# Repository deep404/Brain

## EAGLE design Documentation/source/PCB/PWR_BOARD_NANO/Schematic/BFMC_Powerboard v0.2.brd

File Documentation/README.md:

# BFMC - Documentation Project

This repo contains the sources for the Bosch Future Mobility Challenge documentation. 
Find it at this [link](https://bosch-future-mobility-challenge-documentation.readthedocs-hosted.com)

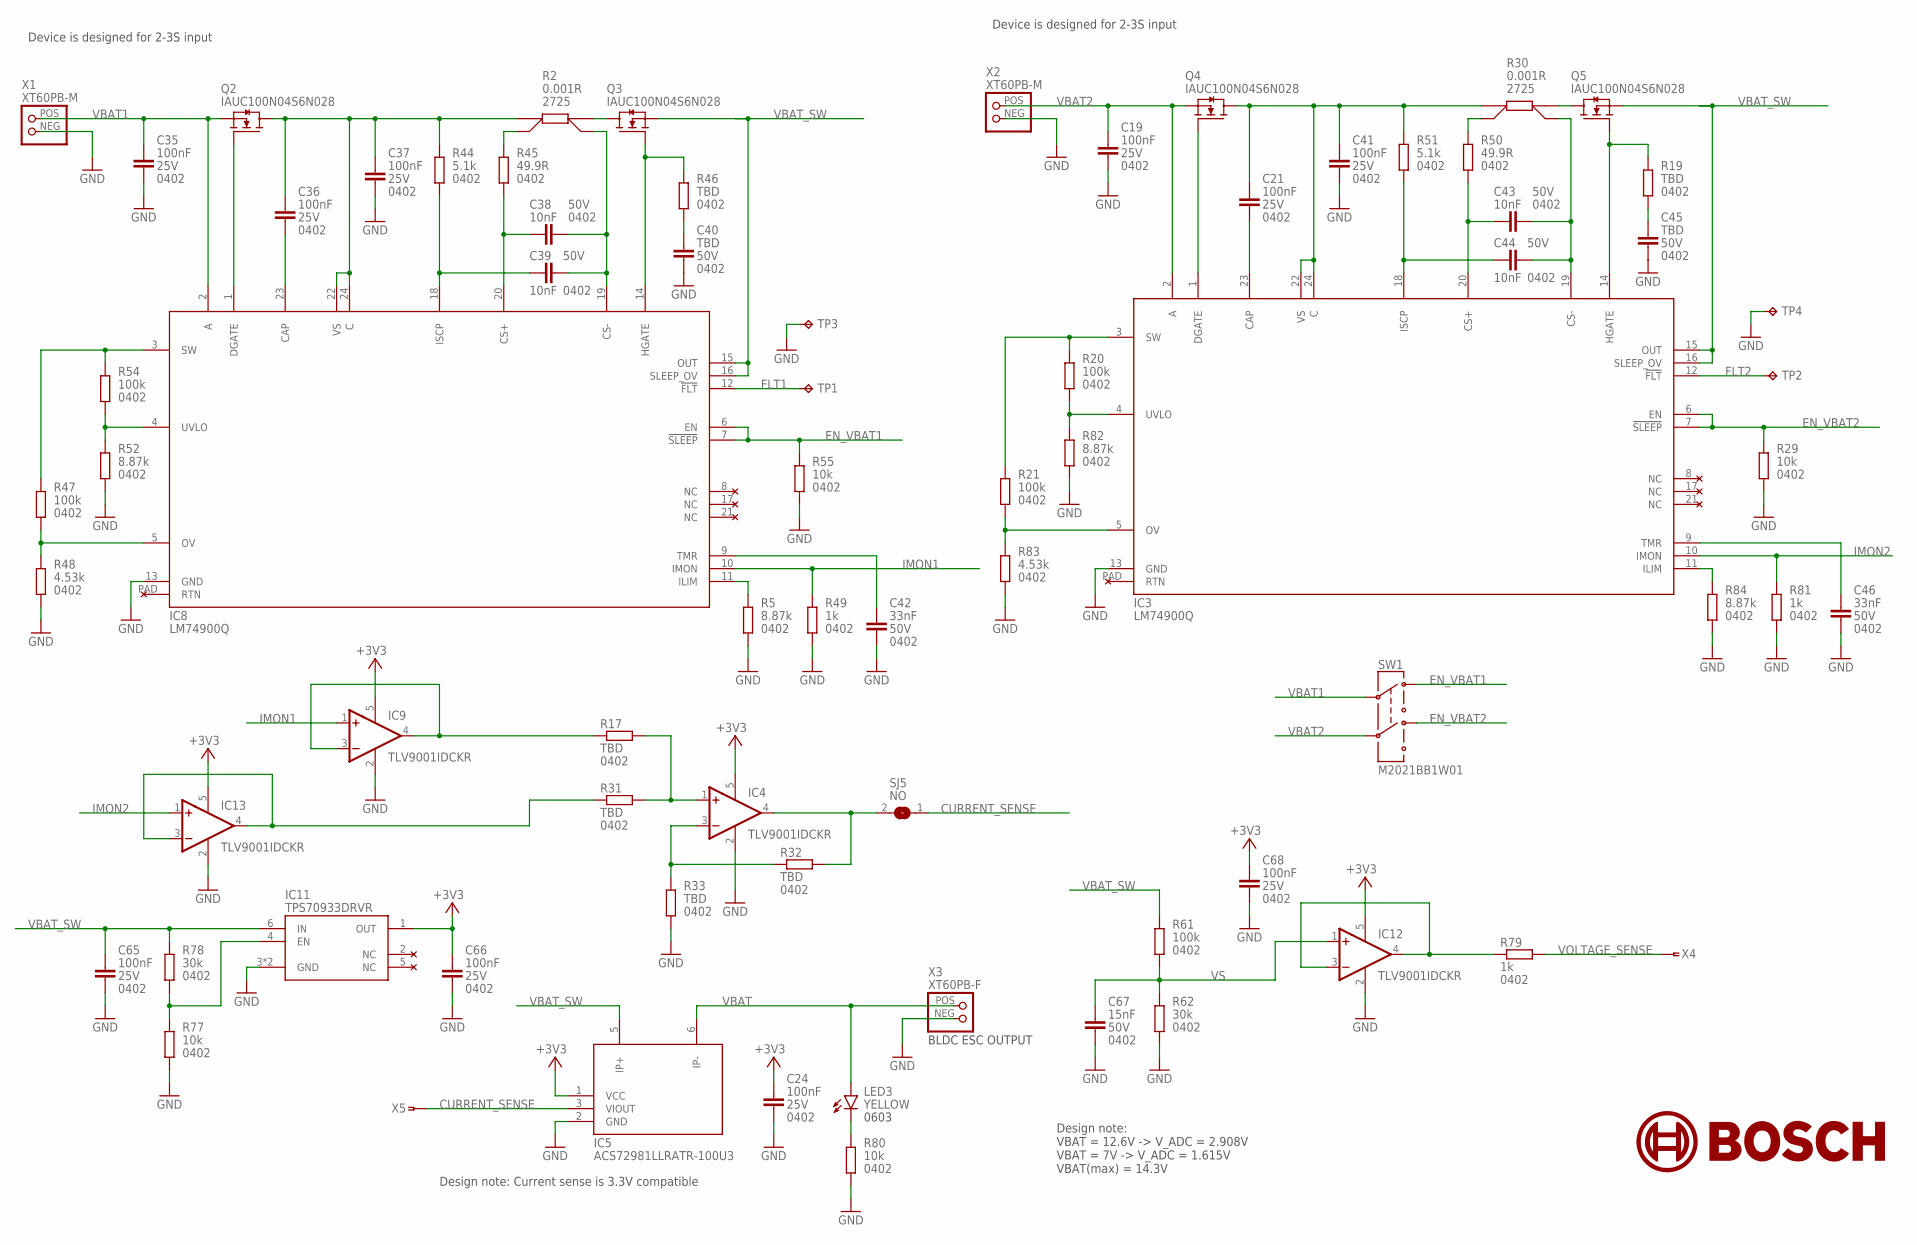
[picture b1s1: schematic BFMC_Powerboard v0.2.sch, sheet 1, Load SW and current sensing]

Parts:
C19, C21, C24, C35, C36, C37, C41, C65, C66, C68: 100nF; C0402_IPC
C38, C39, C43, C44: 10nF; C0402_IPC
C40, C45: TBD; C0402_IPC
C42, C46: 33nF; C0402_IPC
C67: 15nF; C0402_IPC
IC3, IC8: LM74900Q; QFN24-4X4
IC4, IC9, IC12, IC13: TLV9001IDCKR; SC70-5
IC5: ACS72981LLRATR-100U3; ACS72981
IC11: TPS70933DRVR; WSON6_2X2MM_NO_SILK
LED3: YELLOW; CHIPLED_0603
Q2, Q3, Q4, Q5: IAUC100N04S6N028; PG-TDSON-8
R2, R30: 0.001R; CRS272
R5, R52, R82, R84: 8.87k; R0402_IPC
R17, R19, R31, R32, R33, R46: TBD; R0402_IPC
R20, R21, R47, R54, R61: 100k; R0402_IPC
R29, R55, R77, R80: 10k; R0402_IPC
R44, R51: 5.1k; R0402_IPC
R45, R50: 49.9R; R0402_IPC
R48, R83: 4.53k; R0402_IPC
R49, R79, R81: 1k; R0402_IPC
R62, R78: 30k; R0402_IPC
SJ5: NO; SJ_1X1.5_NO
SW1: M2021BB1W01
TP1, TP2, TP3, TP4: TPTP13R; TP13R
X1, X2: XT60PB-M; XT60PB
X3: XT60PB-F; XT60PB
X4, X5: ZFKDSA1-W-6,35; 1704994

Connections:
+3V3: C24.1, C66.1, C68.1, IC4.5 (V+), IC5.1 (VCC), IC9.5 (V+), IC11.1 (OUT), IC12.5 (V+), IC13.5 (V+); also elsewhere on the board
CURRENT_SENSE: IC5.3 (VIOUT), SJ5.1, X5.1, X5.2
EN_VBAT1: IC8.6 (EN), IC8.7 (!SLEEP), R55.2, SW1.3
EN_VBAT2: IC3.6 (EN), IC3.7 (!SLEEP), R29.2, SW1.6
FLT1: IC8.12 (!FLT), TP1.TP
FLT2: IC3.12 (!FLT), TP2.TP
GND: C19.2, C24.2, C35.2, C37.2, C40.1, C41.2, C42.2, C45.1, C46.2, C65.2, C66.2, C67.2, C68.2, IC3.13 (GND), IC4.2 (V-), IC5.2 (GND), IC8.13 (GND), IC9.2 (V-), IC11.3 (GND), IC11.EP (GND), IC12.2 (V-), IC13.2 (V-), R5.1, R29.1, R33.1, R48.1, R49.1, R52.1, R55.1, R62.1, R77.1, R80.1, R81.1, R82.1, R83.1, R84.1, TP3.TP, TP4.TP, X1.NEG (2), X2.NEG (2), X3.NEG (2); also elsewhere on the board
IMON1: IC8.10 (IMON), IC9.1 (+IN), R49.2
IMON2: IC3.10 (IMON), IC13.1 (+IN), R81.2
unnamed: IC8.1 (DGATE), Q2.4 (G)
unnamed: IC3.1 (DGATE), Q4.4 (G)
unnamed: C21.2, IC3.23 (CAP)
unnamed: C21.1, C41.1, IC3.22 (VS), IC3.24 (C), Q4.5 (D), Q4.6 (D), Q4.7 (D), Q4.8 (D), Q4.TH (D), R30.1A, R51.2
unnamed: IC3.14 (HGATE), Q5.4 (G), R19.2
unnamed: IC4.1 (+IN), R17.2, R31.2
unnamed: C44.1, IC3.18 (ISCP), R51.1
unnamed: R30.1B, R50.2
unnamed: C43.2, C44.2, IC3.19 (CS-), R30.2B
unnamed: Q5.5 (D), Q5.6 (D), Q5.7 (D), Q5.8 (D), Q5.TH (D), R30.2A
unnamed: IC4.4 (OUT), R32.2, SJ5.2
unnamed: C43.1, IC3.20 (CS+), R50.1
unnamed: C45.2, R19.1
unnamed: IC4.3 (-IN), R32.1, R33.2
unnamed: IC9.3 (-IN), IC9.4 (OUT), R17.1
unnamed: IC13.3 (-IN), IC13.4 (OUT), R31.1
unnamed: C36.2, IC8.23 (CAP)
unnamed: C36.1, C37.1, IC8.22 (VS), IC8.24 (C), Q2.5 (D), Q2.6 (D), Q2.7 (D), Q2.8 (D), Q2.TH (D), R2.1A, R44.2
unnamed: IC8.14 (HGATE), Q3.4 (G), R46.2
unnamed: C39.1, IC8.18 (ISCP), R44.1
unnamed: IC8.3 (SW), R47.2, R54.2
unnamed: R2.1B, R45.2
unnamed: C38.2, C39.2, IC8.19 (CS-), R2.2B
unnamed: Q3.5 (D), Q3.6 (D), Q3.7 (D), Q3.8 (D), Q3.TH (D), R2.2A
unnamed: C38.1, IC8.20 (CS+), R45.1
unnamed: C40.2, R46.1
unnamed: IC8.11 (ILIM), R5.2
unnamed: IC3.11 (ILIM), R84.2
unnamed: C42.1, IC8.9 (TMR)
unnamed: IC8.4 (UVLO), R52.2, R54.1
unnamed: IC8.5 (OV), R47.1, R48.2
unnamed: IC12.3 (-IN), IC12.4 (OUT), R79.1
unnamed: LED3.C, R80.2
unnamed: IC11.4 (EN), R77.2, R78.1
unnamed: C46.1, IC3.9 (TMR)
unnamed: IC3.3 (SW), R20.2, R21.2
unnamed: IC3.4 (UVLO), R20.1, R82.2
unnamed: IC3.5 (OV), R21.1, R83.2
VBAT: IC5.6 (IP-), LED3.A, X3.POS (1); also elsewhere on the board
VBAT1: C35.1, IC8.2 (A), Q2.1 (S), Q2.2 (S), Q2.3 (S), SW1.2, X1.POS (1)
VBAT2: C19.1, IC3.2 (A), Q4.1 (S), Q4.2 (S), Q4.3 (S), SW1.5, X2.POS (1)
VBAT_SW: C65.1, IC3.15 (OUT), IC3.16 (SLEEP_OV), IC5.5 (IP+), IC8.15 (OUT), IC8.16 (SLEEP_OV), IC11.6 (IN), Q3.1 (S), Q3.2 (S), Q3.3 (S), Q5.1 (S), Q5.2 (S), Q5.3 (S), R61.2, R78.2
VOLTAGE_SENSE: R79.2, X4.1, X4.2
VS: C67.1, IC12.1 (+IN), R61.1, R62.2

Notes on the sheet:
BLDC ESC OUTPUT
Device is designed for 2-3S input
Design note: Current sense is 3.3V compatible
Design note: VBAT = 12.6V -> V_ADC = 2.908V VBAT = 7V -> V_ADC = 1.615V VBAT(max) = 14.3V

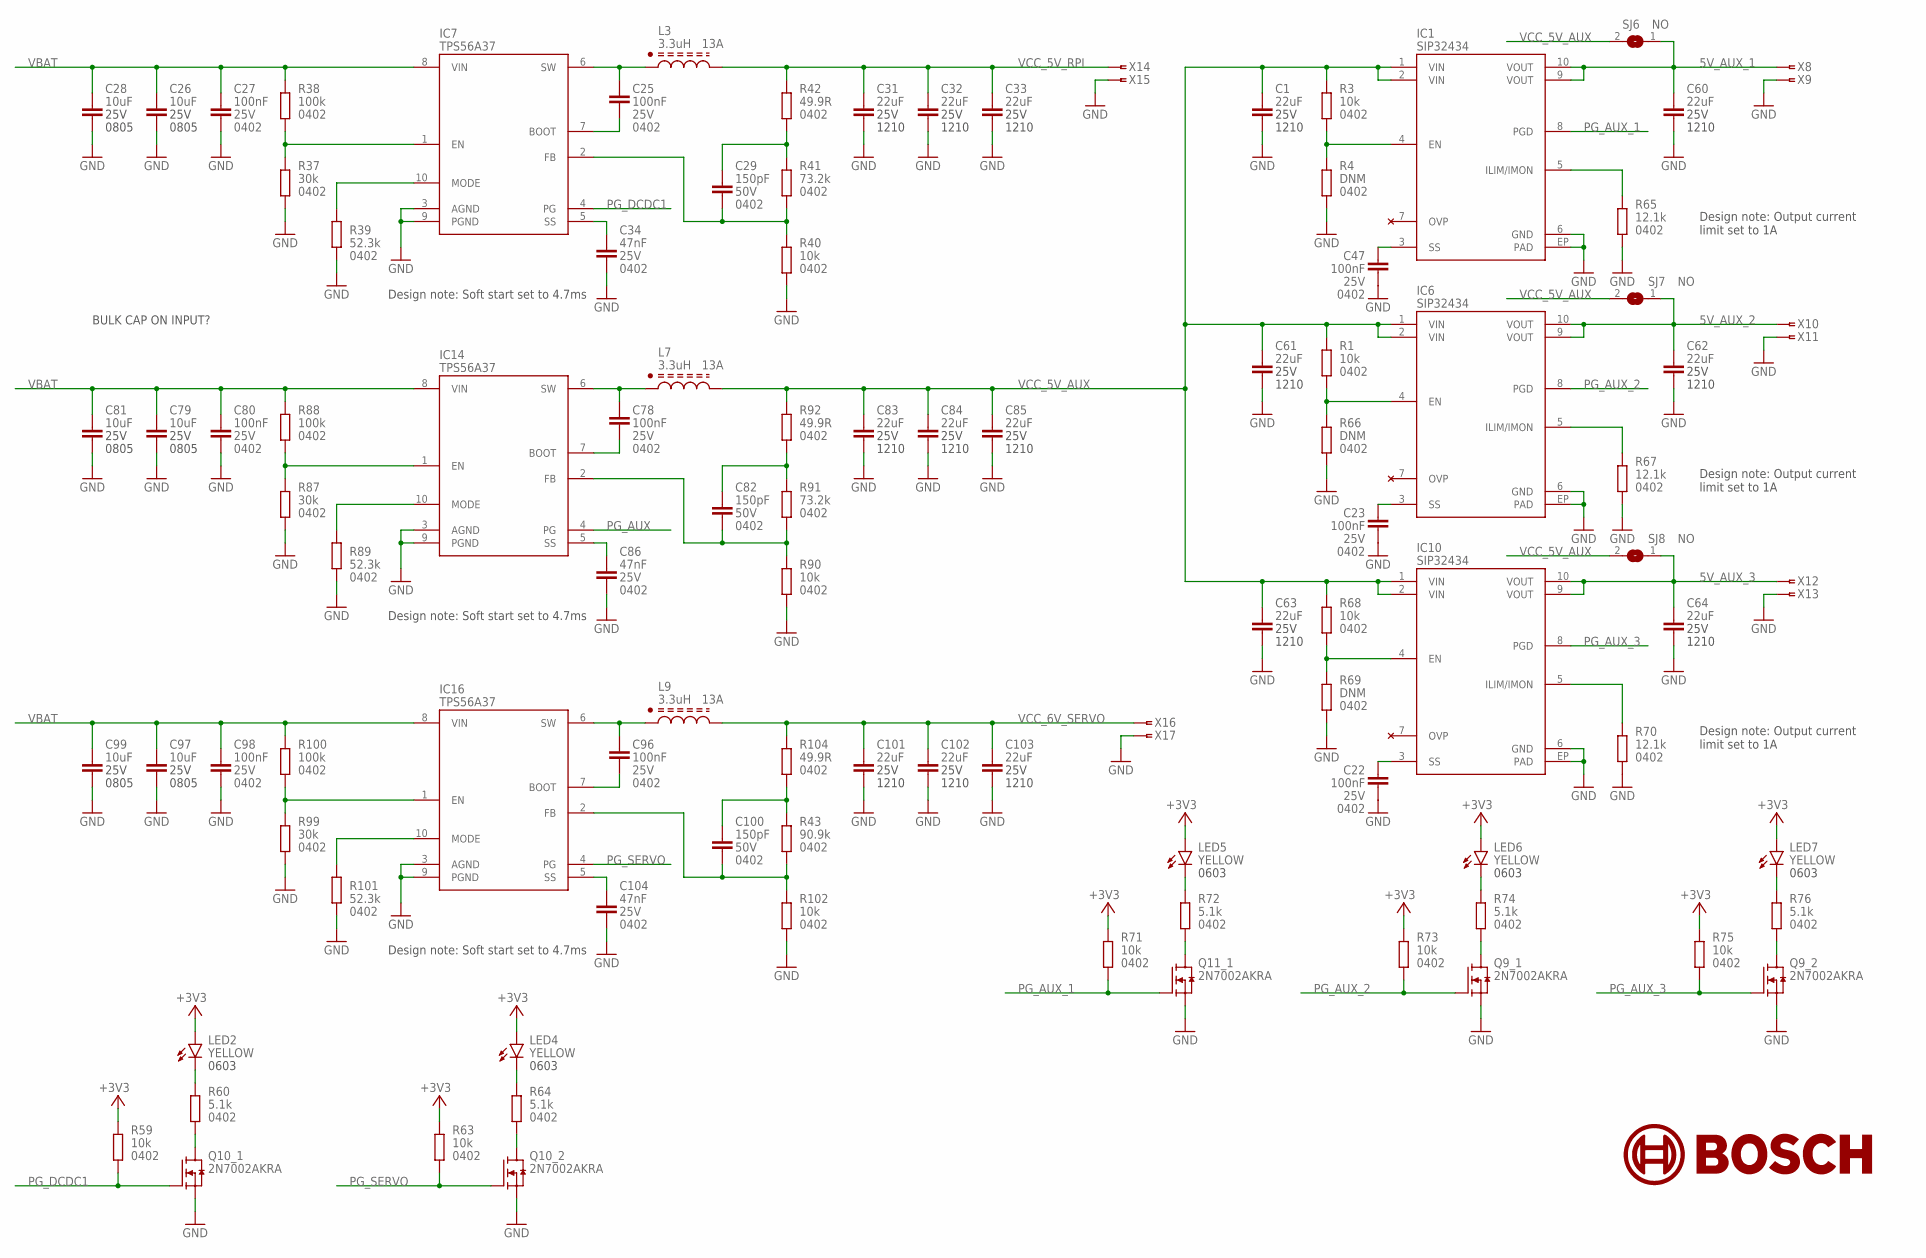
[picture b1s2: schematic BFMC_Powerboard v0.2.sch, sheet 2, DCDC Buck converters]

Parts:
C1, C31, C32, C33, C60, C61, C62, C63, C64, C83, C84, C85, C101, C102, C103: 22uF; C1210
C22, C23, C25, C27, C47, C78, C80, C96, C98: 100nF; C0402_IPC
C26, C28, C79, C81, C97, C99: 10uF; C0805
C29, C82, C100: 150pF; C0402_IPC
C34, C86, C104: 47nF; C0402_IPC
IC1, IC6, IC10: SIP32434; DFN10-3X3
IC7, IC14, IC16: TPS56A37; VQFN-HR-RPA
L3, L7, L9: 3.3uH; EXLA1V0705
LED2, LED4, LED5, LED6, LED7: YELLOW; CHIPLED_0603
Q9, Q10, Q11: 2N7002AKRA; DFN1412-6
R1, R3, R40, R59, R63, R68, R71, R73, R75, R90, R102: 10k; R0402_IPC
R4, R66, R69: DNM; R0402_IPC
R37, R87, R99: 30k; R0402_IPC
R38, R88, R100: 100k; R0402_IPC
R39, R89, R101: 52.3k; R0402_IPC
R41, R91: 73.2k; R0402_IPC
R42, R92, R104: 49.9R; R0402_IPC
R43: 90.9k; R0402_IPC
R60, R64, R72, R74, R76: 5.1k; R0402_IPC
R65, R67, R70: 12.1k; R0402_IPC
SJ6, SJ7, SJ8: NO; SJ_1X1.5_NO
X8, X9, X10, X11, X12, X13, X14, X15, X16, X17: ZFKDSA1-W-6,35; 1704994

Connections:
5V_AUX_1: C60.1, IC1.9 (VOUT), IC1.10 (VOUT), SJ6.1, X8.1, X8.2
5V_AUX_2: C62.1, IC6.9 (VOUT), IC6.10 (VOUT), SJ7.1, X10.1, X10.2
5V_AUX_3: C64.1, IC10.9 (VOUT), IC10.10 (VOUT), SJ8.1, X12.1, X12.2
+3V3: LED2.A, LED4.A, LED5.A, LED6.A, LED7.A, R59.2, R63.2, R71.2, R73.2, R75.2; also elsewhere on the board
GND: C1.2, C22.2, C23.2, C26.2, C27.2, C28.2, C31.2, C32.2, C33.2, C34.2, C47.2, C60.2, C61.2, C62.2, C63.2, C64.2, C79.2, C80.2, C81.2, C83.2, C84.2, C85.2, C86.2, C97.2, C98.2, C99.2, C101.2, C102.2, C103.2, C104.2, IC1.6 (GND), IC1.EP (PAD), IC6.6 (GND), IC6.EP (PAD), IC7.3 (AGND), IC7.9 (PGND), IC10.6 (GND), IC10.EP (PAD), IC14.3 (AGND), IC14.9 (PGND), IC16.3 (AGND), IC16.9 (PGND), Q9.1 (S), Q9.4 (S), Q10.1 (S), Q10.4 (S), Q11.1 (S), R4.1, R37.1, R39.1, R40.1, R65.1, R66.1, R67.1, R69.1, R70.1, R87.1, R89.1, R90.1, R99.1, R101.1, R102.1, X9.1, X9.2, X11.1, X11.2, X13.1, X13.2, X15.1, X15.2, X17.1, X17.2; also elsewhere on the board
unnamed: IC6.5 (ILIM/IMON), R67.2
unnamed: IC1.5 (ILIM/IMON), R65.2
unnamed: IC1.4 (EN), R3.1, R4.2
unnamed: C22.1, IC10.3 (SS)
unnamed: C23.1, IC6.3 (SS)
unnamed: C47.1, IC1.3 (SS)
unnamed: C25.1, IC7.6 (SW), L3.1
unnamed: C25.2, IC7.7 (BOOT)
unnamed: C34.1, IC7.5 (SS)
unnamed: IC7.1 (EN), R37.2, R38.1
unnamed: C29.2, IC7.2 (FB), R40.2, R41.1
unnamed: IC7.10 (MODE), R39.2
unnamed: C29.1, R41.2, R42.1
unnamed: Q10.6 (D), Q10.7 (D), R60.1
unnamed: LED2.C, R60.2
unnamed: Q10.3 (D), Q10.8 (D), R64.1
unnamed: LED4.C, R64.2
unnamed: IC6.4 (EN), R1.1, R66.2
unnamed: IC10.5 (ILIM/IMON), R70.2
unnamed: IC10.4 (EN), R68.1, R69.2
unnamed: Q11.6 (D), Q11.7 (D), R72.1
unnamed: LED5.C, R72.2
unnamed: Q9.6 (D), Q9.7 (D), R74.1
unnamed: LED6.C, R74.2
unnamed: Q9.3 (D), Q9.8 (D), R76.1
unnamed: LED7.C, R76.2
unnamed: C78.1, IC14.6 (SW), L7.1
unnamed: C78.2, IC14.7 (BOOT)
unnamed: IC14.1 (EN), R87.2, R88.1
unnamed: IC14.10 (MODE), R89.2
unnamed: C82.2, IC14.2 (FB), R90.2, R91.1
unnamed: C82.1, R91.2, R92.1
unnamed: C86.1, IC14.5 (SS)
unnamed: C96.1, IC16.6 (SW), L9.1
unnamed: C96.2, IC16.7 (BOOT)
unnamed: IC16.1 (EN), R99.2, R100.1
unnamed: IC16.10 (MODE), R101.2
unnamed: C100.2, IC16.2 (FB), R43.1, R102.2
unnamed: C100.1, R43.2, R104.1
unnamed: C104.1, IC16.5 (SS)
PG_AUX: IC14.4 (PG)
PG_AUX_1: IC1.8 (PGD), Q11.2 (G), R71.1
PG_AUX_2: IC6.8 (PGD), Q9.2 (G), R73.1
PG_AUX_3: IC10.8 (PGD), Q9.5 (G), R75.1
PG_DCDC1: IC7.4 (PG), Q10.2 (G), R59.1
PG_SERVO: IC16.4 (PG), Q10.5 (G), R63.1
VBAT: C26.1, C27.1, C28.1, C79.1, C80.1, C81.1, C97.1, C98.1, C99.1, IC7.8 (VIN), IC14.8 (VIN), IC16.8 (VIN), R38.2, R88.2, R100.2; also elsewhere on the board
VCC_5V_AUX: C1.1, C61.1, C63.1, C83.1, C84.1, C85.1, IC1.1 (VIN), IC1.2 (VIN), IC6.1 (VIN), IC6.2 (VIN), IC10.1 (VIN), IC10.2 (VIN), L7.2, R1.2, R3.2, R68.2, R92.2, SJ6.2, SJ7.2, SJ8.2; also elsewhere on the board
VCC_5V_RPI: C31.1, C32.1, C33.1, L3.2, R42.2, X14.1, X14.2
VCC_6V_SERVO: C101.1, C102.1, C103.1, L9.2, R104.2, X16.1, X16.2

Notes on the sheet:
Design note: Soft start set to 4.7ms
BULK CAP ON INPUT?
Design note: Output current limit set to 1A

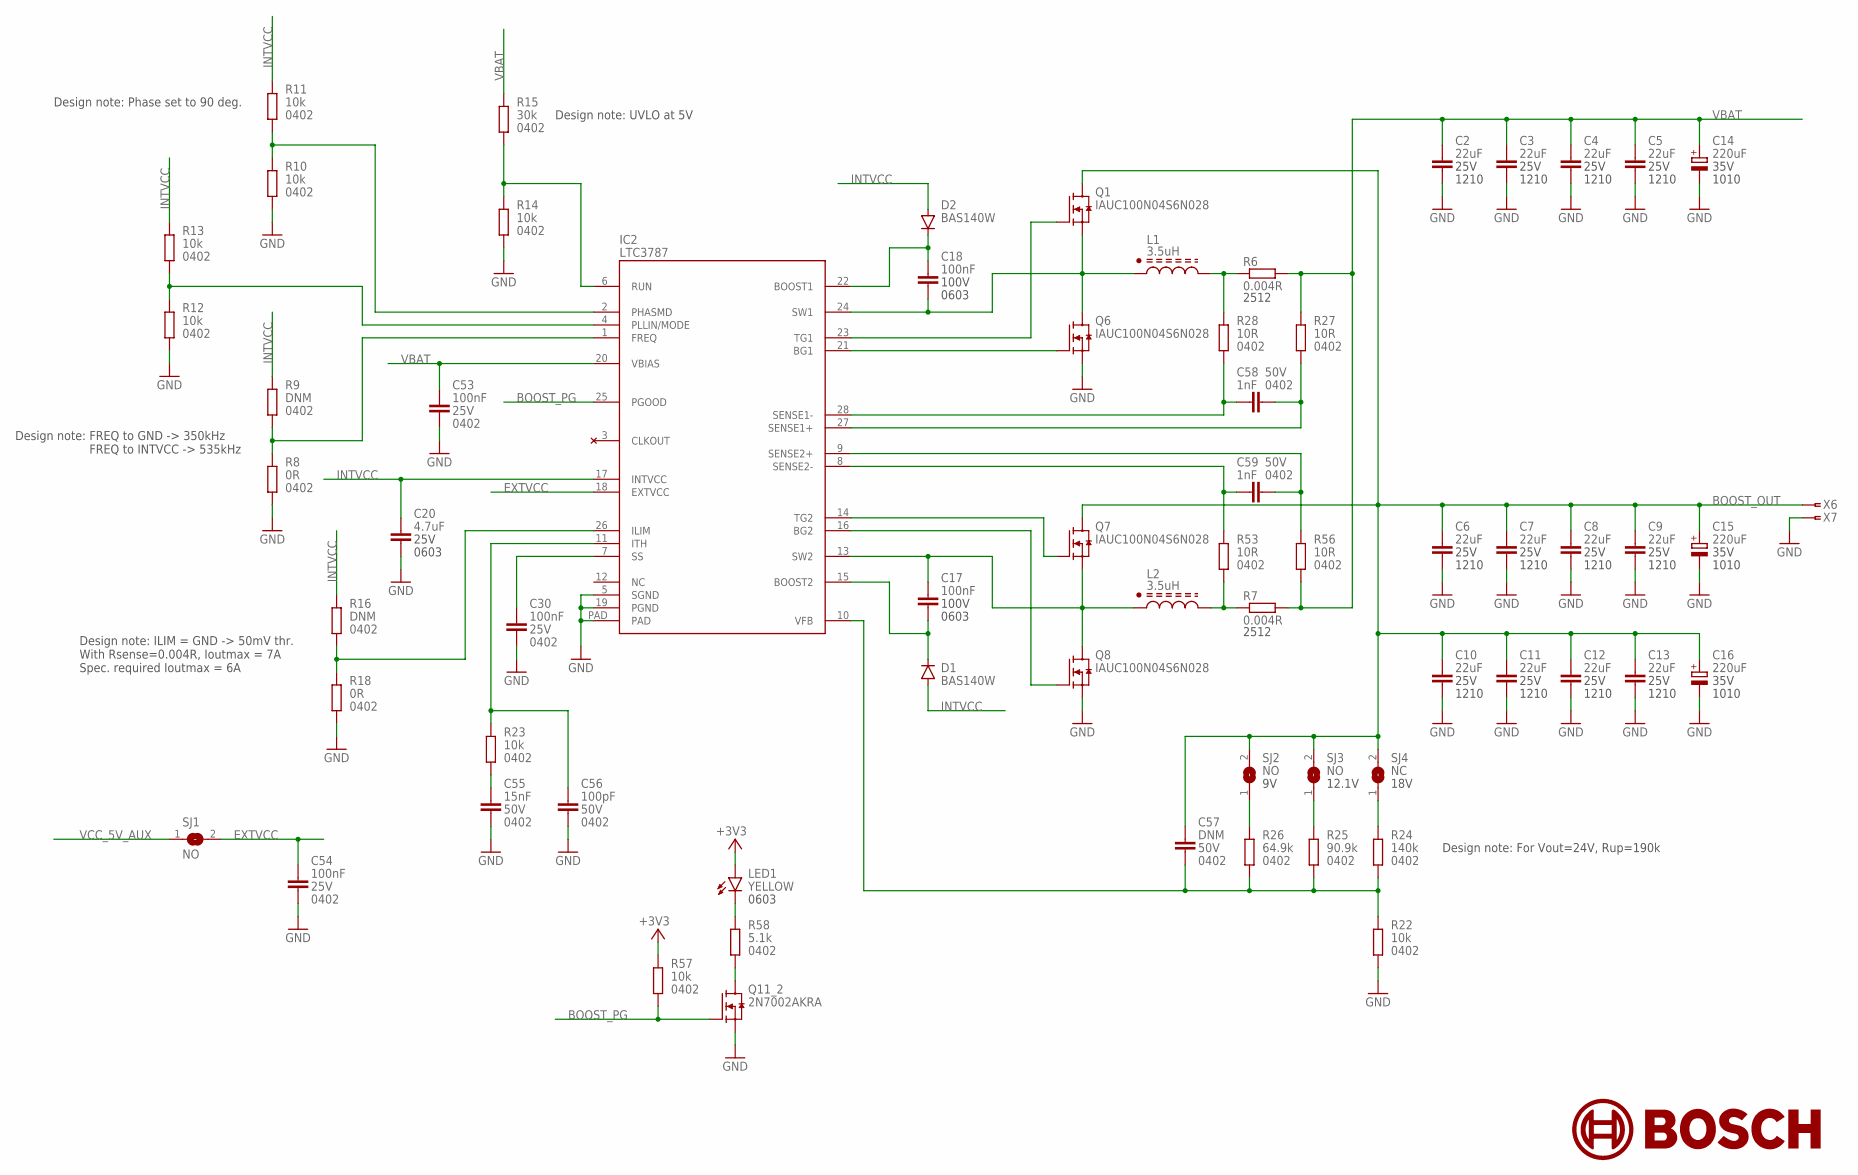
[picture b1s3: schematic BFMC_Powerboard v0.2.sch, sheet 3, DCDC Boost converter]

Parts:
C2, C3, C4, C5, C6, C7, C8, C9, C10, C11, C12, C13: 22uF; C1210
C14, C15, C16: 220uF; CAP_POL_1010
C17, C18: 100nF; C0603
C20: 4.7uF; C0603
C30, C53, C54: 100nF; C0402_IPC
C55: 15nF; C0402_IPC
C56: 100pF; C0402_IPC
C57: DNM; C0402_IPC
C58, C59: 1nF; C0402_IPC
D1, D2: BAS140W; SOD323-R
IC2: LTC3787; UFD-QFN28-4X5MM
L1, L2: 3.5uH; 7447709003
LED1: YELLOW; CHIPLED_0603
Q1, Q6, Q7, Q8: IAUC100N04S6N028; PG-TDSON-8
Q11: 2N7002AKRA; DFN1412-6
R6, R7: 0.004R; R2512
R8, R18: 0R; R0402_IPC
R9, R16: DNM; R0402_IPC
R10, R11, R12, R13, R14, R22, R23, R57: 10k; R0402_IPC
R15: 30k; R0402_IPC
R24: 140k; R0402_IPC
R25: 90.9k; R0402_IPC
R26: 64.9k; R0402_IPC
R27, R28, R53, R56: 10R; R0402_IPC
R58: 5.1k; R0402_IPC
SJ1, SJ2, SJ3: NO; SJ_1X1.5_NO
SJ4: NC; SJ_1X1.5_NO
X6, X7: ZFKDSA1-W-6,35; 1704994

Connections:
+3V3: LED1.A, R57.2; also elsewhere on the board
BOOST_OUT: C6.1, C7.1, C8.1, C9.1, C10.1, C11.1, C12.1, C13.1, C15.2 (+), C16.2 (+), C57.1, Q1.5 (D), Q1.6 (D), Q1.7 (D), Q1.8 (D), Q1.TH (D), Q7.5 (D), Q7.6 (D), Q7.7 (D), Q7.8 (D), Q7.TH (D), SJ2.2, SJ3.2, SJ4.2, X6.1, X6.2
BOOST_PG: IC2.25 (PGOOD), Q11.5 (G), R57.1
EXTVCC: C54.1, IC2.18 (EXTVCC), SJ1.2
GND: C2.2, C3.2, C4.2, C5.2, C6.2, C7.2, C8.2, C9.2, C10.2, C11.2, C12.2, C13.2, C14.1 (-), C15.1 (-), C16.1 (-), C20.2, C30.2, C53.2, C54.2, C55.2, C56.2, IC2.5 (SGND), IC2.19 (PGND), IC2.PAD, Q6.1 (S), Q6.2 (S), Q6.3 (S), Q8.1 (S), Q8.2 (S), Q8.3 (S), Q11.4 (S), R8.1, R10.1, R12.1, R14.1, R18.1, R22.1, X7.1, X7.2; also elsewhere on the board
INTVCC: C20.1, D1.A, D2.A, IC2.17 (INTVCC), R9.2, R11.2, R13.2, R16.2
unnamed: IC2.23 (TG1), Q1.4 (G)
unnamed: IC2.21 (BG1), Q6.4 (G)
unnamed: IC2.14 (TG2), Q7.4 (G)
unnamed: IC2.16 (BG2), Q8.4 (G)
unnamed: C17.1, IC2.13 (SW2), L2.1, Q7.1 (S), Q7.2 (S), Q7.3 (S), Q8.5 (D), Q8.6 (D), Q8.7 (D), Q8.8 (D), Q8.TH (D)
unnamed: C18.2, IC2.24 (SW1), L1.1, Q1.1 (S), Q1.2 (S), Q1.3 (S), Q6.5 (D), Q6.6 (D), Q6.7 (D), Q6.8 (D), Q6.TH (D)
unnamed: C58.1, IC2.28 (SENSE1-), R28.1
unnamed: C59.1, IC2.8 (SENSE2-), R53.2
unnamed: C17.2, D1.C, IC2.15 (BOOST2)
unnamed: C18.1, D2.C, IC2.22 (BOOST1)
unnamed: IC2.1 (FREQ), R8.2, R9.1
unnamed: IC2.4 (PLLIN/MODE), R12.2, R13.1
unnamed: C57.2, IC2.10 (VFB), R22.2, R24.2, R25.1, R26.1
unnamed: IC2.2 (PHASMD), R10.2, R11.1
unnamed: C30.1, IC2.7 (SS)
unnamed: IC2.6 (RUN), R14.2, R15.1
unnamed: C56.1, IC2.11 (ITH), R23.2
unnamed: IC2.26 (ILIM), R16.1, R18.2
unnamed: C55.1, R23.1
unnamed: R24.1, SJ4.1
unnamed: R26.2, SJ2.1
unnamed: R25.2, SJ3.1
unnamed: L1.2, R6.1, R28.2
unnamed: C58.2, IC2.27 (SENSE1+), R27.1
unnamed: L2.2, R7.1, R53.1
unnamed: C59.2, IC2.9 (SENSE2+), R56.2
unnamed: Q11.3 (D), Q11.8 (D), R58.1
unnamed: LED1.C, R58.2
VBAT: C2.1, C3.1, C4.1, C5.1, C14.2 (+), C53.1, IC2.20 (VBIAS), R6.2, R7.2, R15.2, R27.2, R56.1; also elsewhere on the board
VCC_5V_AUX: SJ1.1; also elsewhere on the board

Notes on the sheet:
Design note: FREQ to GND -> 350kHz FREQ to INTVCC -> 535kHz
Design note: Phase set to 90 deg.
Design note: UVLO at 5V
Design note: ILIM = GND -> 50mV thr. With Rsense=0.004R, Ioutmax = 7A Spec. required Ioutmax = 6A
12.1V
18V
Design note: For Vout=24V, Rup=190k

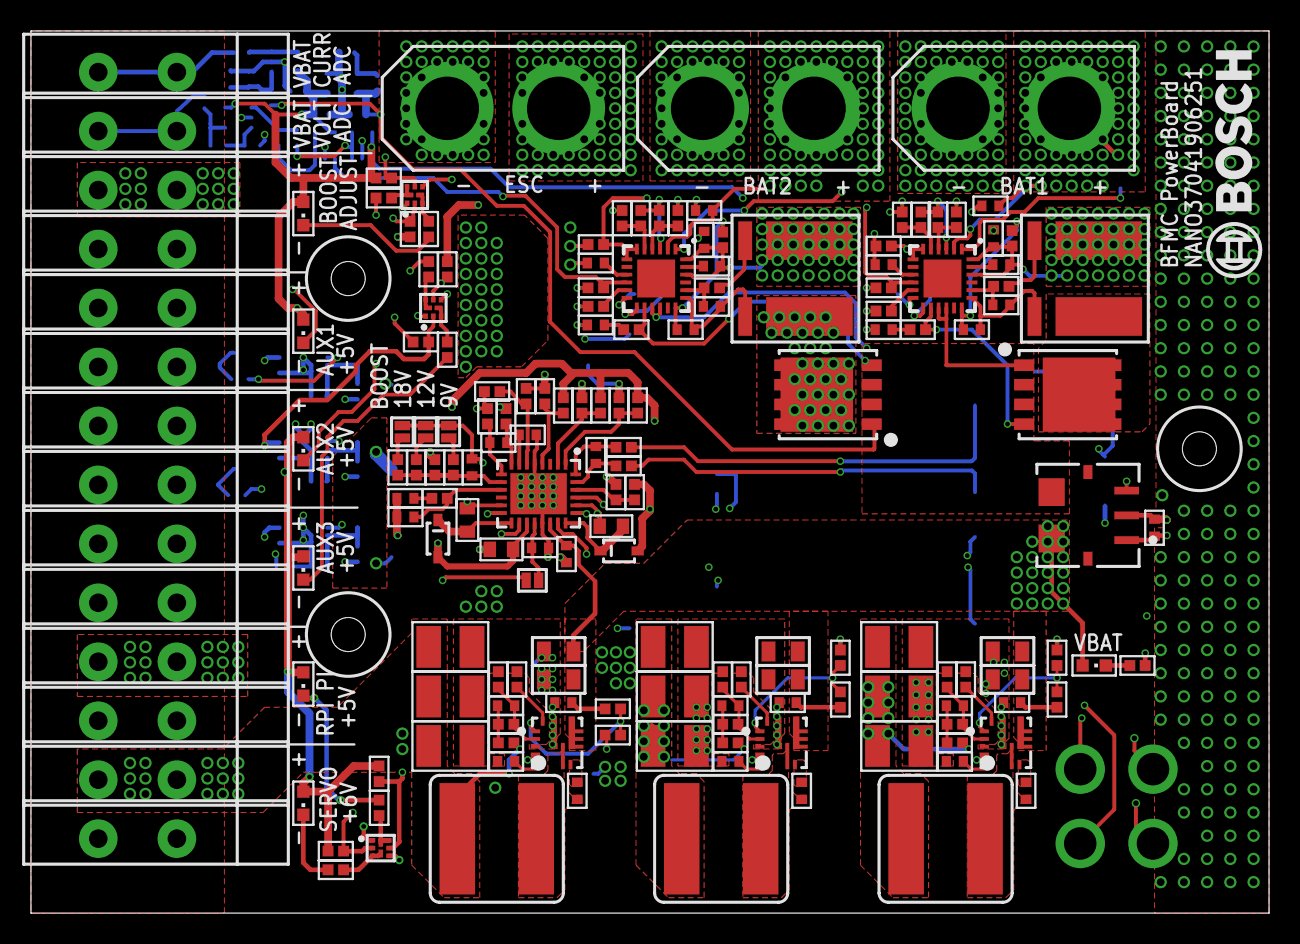
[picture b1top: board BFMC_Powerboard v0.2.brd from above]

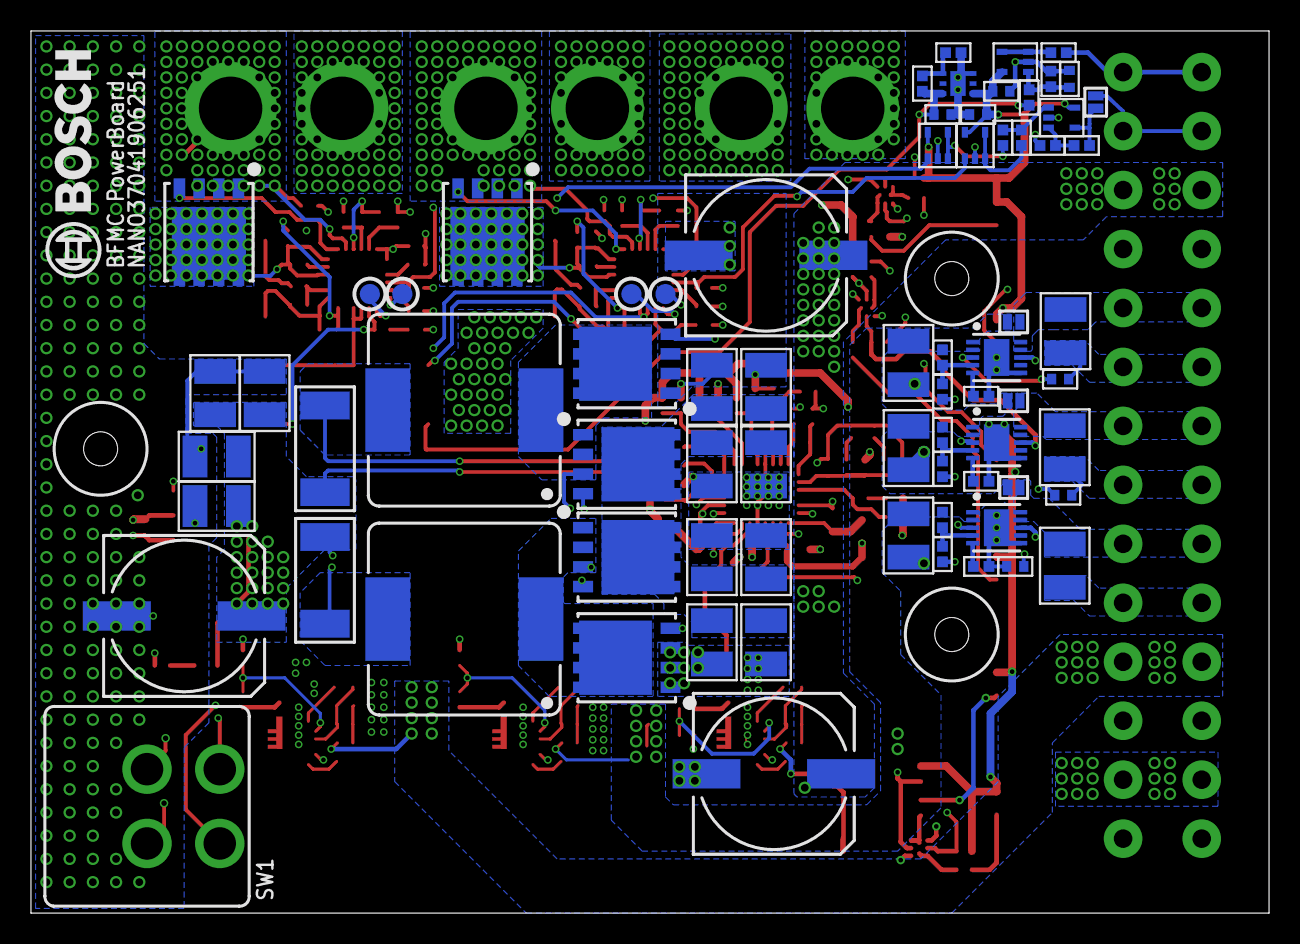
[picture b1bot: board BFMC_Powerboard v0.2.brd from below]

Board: 6 copper layers, 80.0 x 57.0 mm, 245 parts (74 on the bottom side), 136 nets.

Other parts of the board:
U$1, U$2: BOSCH_15

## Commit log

2026-02-19 attach Documentation
2026-02-19 update requirements for traffic sign detection model
2026-02-19 update dashboard frontend
2026-02-19 remote library for picamera
2026-02-19 table state json
2026-02-19 define service for traffic sign detection model
2026-02-19 correct error with temperature sensor info
2026-02-19 upload nano and d nd small traffic sign detection model yolo
2026-02-19 define video loop infinte vs live video
2026-02-19 upload video for for infinite loop
2026-02-19 upload video for iinfinite loop for test
2026-02-19 add requirements for lane assist
2026-02-20 define lane assistant service
2026-03-06 add route planning and solve bug with paralel services
